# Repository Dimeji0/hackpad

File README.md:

# hackpad
# hackpad

PCB design

The PCB Schematic

Features:
Firmware built using QMK
1. 3 cherry MX style keys
2. EC11 rotary encoder with a switch
3. Xiaou RP 2040
The 3 keys should simply output A,B, and C and then pressing the switch on the encoder will allow it to switch to video playback controls. May not be the final plan for the keys

   CAD model

Note model is only designed not programmed or build yet
This was made so I could set keybind in video games and connect them to my hackpad for easier playing so thats why I made it and what it'll be used for.

**BOM**
1. 3x MX cherry style keys
2. EC11 rotary encoder with  switch
3. Soldering kit
4. Xiaou RP2040
5. 1x case (3 printed parts)

Thats all the stuff I'm sure you need, as for diodes and all that not sure how to use those yet if I'm being honest I was gonna learn and figure that part out when I get the starter kit and other stuff.

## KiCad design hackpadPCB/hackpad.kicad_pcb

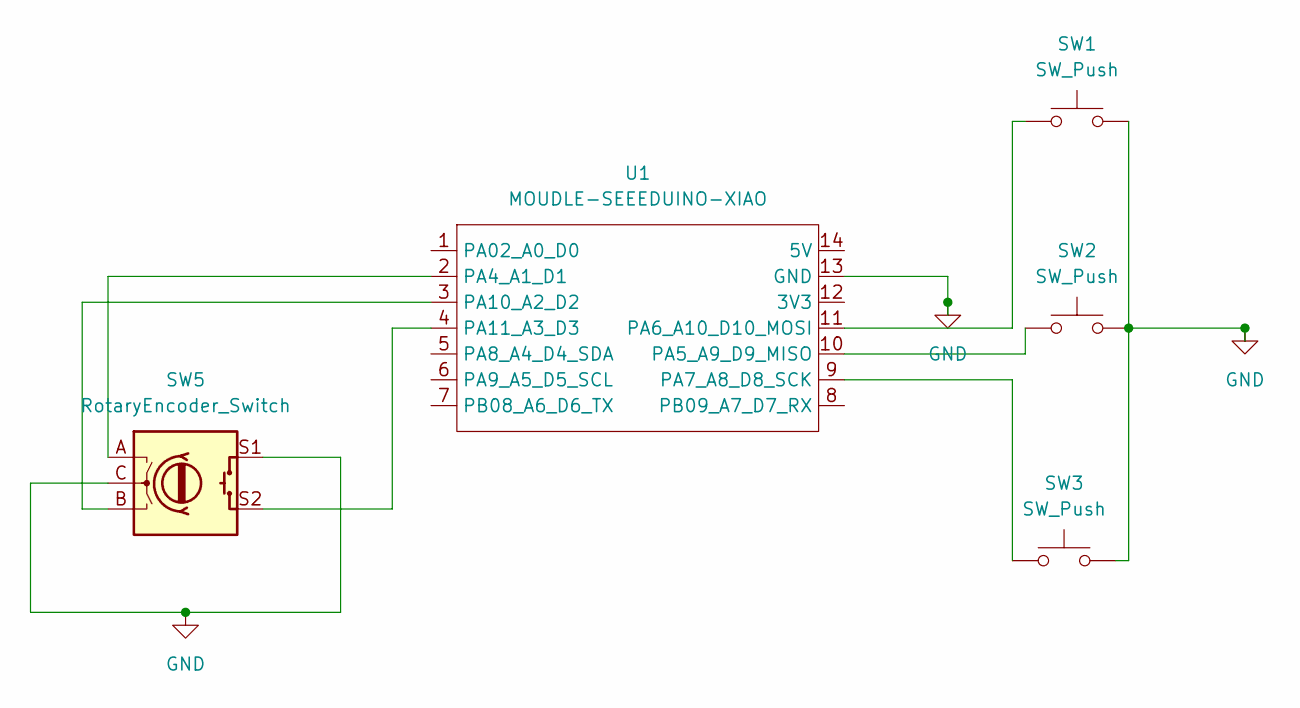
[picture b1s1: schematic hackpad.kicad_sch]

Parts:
SW1, SW2, SW3: SW_Push; SW_Cherry_MX_1.00u_PCB
SW5: RotaryEncoder_Switch; RotaryEncoder_Alps_EC11E-Switch_Vertical_H20mm
U1: MOUDLE-SEEEDUINO-XIAO; XIAO-Generic-Hybrid-14P-2.54-21X17.8MM

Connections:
GND: SW1.2, SW2.2, SW3.2, SW5.C, SW5.S1, U1.13 (GND)
unnamed: SW5.A, U1.2 (PA4_A1_D1)
unnamed: SW2.1, U1.10 (PA5_A9_D9_MISO)
unnamed: SW1.1, U1.11 (PA6_A10_D10_MOSI)
unnamed: SW3.1, U1.9 (PA7_A8_D8_SCK)
unnamed: SW5.B, U1.3 (PA10_A2_D2)
unnamed: SW5.S2, U1.4 (PA11_A3_D3)

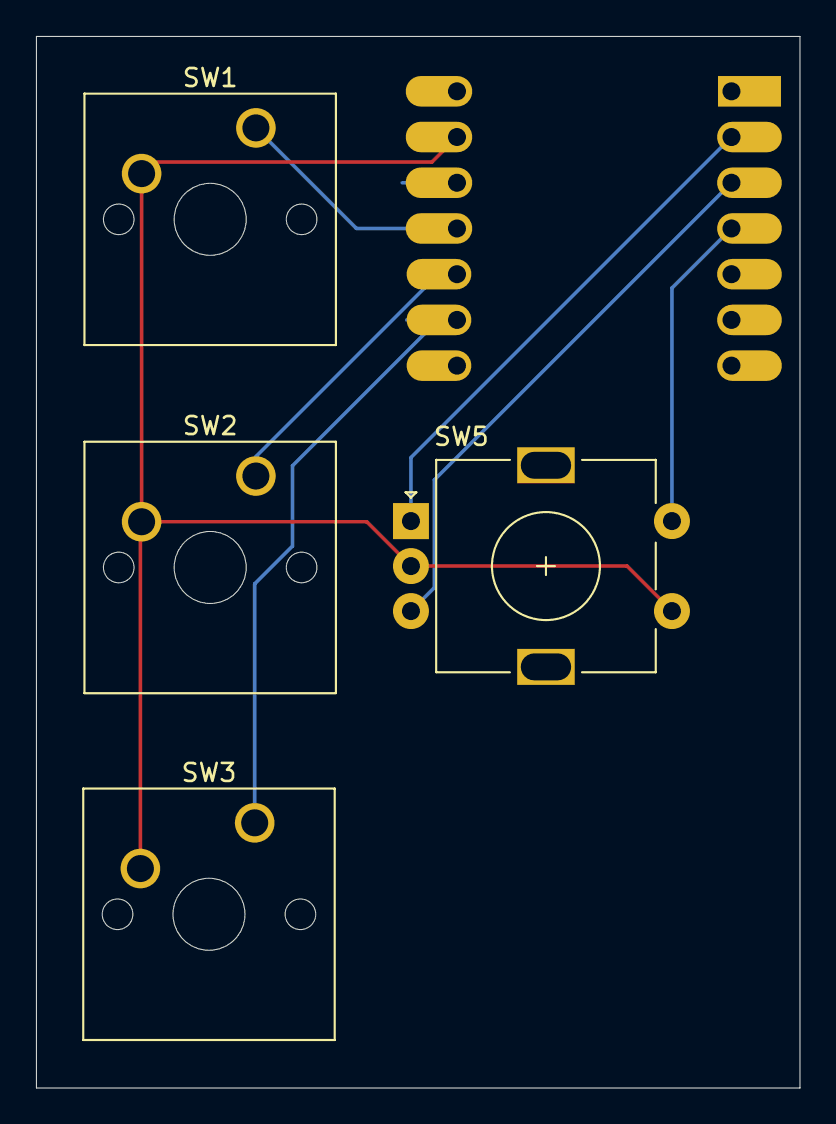
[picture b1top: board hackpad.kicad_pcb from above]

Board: 2 copper layers, 42.4 x 58.4 mm, 5 parts (1 on the bottom side), 7 nets.
